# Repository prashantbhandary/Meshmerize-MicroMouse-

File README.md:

# 🤖 Meshmerize MicroMouse Project

> **A comprehensive autonomous line-following and maze-solving robot project featuring multiple hardware iterations, advanced algorithms, and professional PCB designs.**

## 🏆 Competition Achievements

Our MicroMouse has proven its excellence in prestigious robotics competitions:

- 🥇 **1st Place** - Locus, Pulchowk Campus  
- 🥈 **2nd Place** - Delta 5.0, Dharan IOE  
- 🏅 **5th Place** - Techfest, IIT Bombay 2024

<div align="center">

*Certificate of Achievement from IIT Bombay Techfest 2024*

</div>

---

## 📋 Table of Contents

- [🎯 Project Overview](#-project-overview)
- [✨ Key Features](#-key-features)
- [🔧 Hardware Versions](#-hardware-versions)
- [💻 Software Architecture](#-software-architecture)
- [🚀 Getting Started](#-getting-started)
- [📁 Repository Structure](#-repository-structure)
- [🛠️ Installation & Setup](#️-installation--setup)
- [🎮 Usage Instructions](#-usage-instructions)
- [🧠 Algorithms & Control Systems](#-algorithms--control-systems)
- [📷 Project Gallery](#-project-gallery)
- [🤝 Contributing](#-contributing)
- [📄 License](#-license)

---

## 🎯 Project Overview

The **Meshmerize MicroMouse** is an autonomous robot designed to navigate line-following courses and solve complex mazes. This project showcases the evolution of robotics engineering through multiple hardware iterations, from Arduino Nano-based prototypes to advanced ESP32-powered systems.

### What Makes This Project Special?

- **Multiple Hardware Generations**: Evolution from v1.0 to v3.1 with continuous improvements
- **Dual Platform Support**: Both Arduino Nano and ESP32 implementations
- **Professional PCB Design**: Custom-designed circuit boards using KiCad
- **Advanced Algorithms**: LSRB maze-solving with optimized PID control
- **Competition-Tested**: Proven performance in national and international competitions

---

## ✨ Key Features

### 🎯 **Navigation Capabilities**
- **Line Following**: Precise black/white line detection and following
- **Maze Solving**: Autonomous exploration and shortest path execution
- **Multi-Surface Support**: Adaptable to different track conditions

### ⚡ **Performance Optimization**
- **PID Control System**: Smooth and accurate movement control
- **Speed Management**: Adaptive speed control for different track sections
- **Sensor Calibration**: Advanced sensor tuning for reliable detection

### 🔧 **Hardware Excellence**
- **Custom PCB Design**: Professional circuit board layouts
- **Modular Architecture**: Easy maintenance and upgrades
- **Power Management**: Efficient voltage regulation for all components

---

## 🔧 Hardware Versions

<details>
<summary><strong>Arduino Nano Series</strong></summary>

### Version 1.0 - Prototype
- **Microcontroller**: Arduino Nano
- **Motor Driver**: L293D
- **Sensors**: QTR-8A analog sensor array
- **Status**: Initial prototype and testing phase

### Version 2.0 - Enhanced Performance
- **Microcontroller**: Arduino Nano (optimized)
- **Motor Driver**: SparkFun TB6612FNG
- **Sensors**: 8-channel QTR sensor array
- **Improvements**: Better motor control, enhanced PID tuning
- **PCB**: Custom-designed v2.0 PCB

### Version 3.0/3.1 - Professional Grade
- **Microcontroller**: Arduino Nano
- **Features**: Professional PCB design with improved layout
- **Status**: Competition-ready version

</details>

<details>
<summary><strong>ESP32 Series</strong></summary>

### ESP32 Version 1.0
- **Microcontroller**: ESP32 DevKit
- **Development**: PlatformIO-based development
- **Features**: 
  - Wireless capabilities
  - Higher processing power
  - Advanced sensor integration
- **PCB**: Custom ESP32-based PCB design

</details>

---

## 💻 Software Architecture

### Programming Platforms
- **Arduino IDE**: Traditional Arduino Nano development
- **PlatformIO**: Advanced ESP32 development with better library management

### Key Libraries
```cpp
#include <SparkFun_TB6612.h>  // Motor control library
#include <QTRSensors.h>       // Sensor array library
```

### Algorithm Implementation
- **LSRB Algorithm**: Left-Straight-Right-Back priority maze solving
- **PID Control**: Proportional-Integral-Derivative control for smooth movement
- **Path Optimization**: Shortest path calculation and execution

---

## 🚀 Getting Started

### Prerequisites
- Arduino IDE or PlatformIO
- USB cable for programming
- Basic electronics knowledge
- Robotics track or maze for testing

### Quick Setup
1. **Clone the repository**
   ```bash
   git clone https://github.com/prashantbhandary/Meshmerize-MicroMouse-.git
   cd Meshmerize-MicroMouse-
   ```

2. **Choose your platform**
   - For Arduino Nano: Navigate to `ArduinoNano/` folder
   - For ESP32: Navigate to `Esp32/` folder

3. **Select the appropriate version**
   - Pick the version that matches your hardware setup
   - Latest versions recommended for best performance

---

## 📁 Repository Structure

```
📦 Meshmerize-MicroMouse-
├── 🔧 ArduinoNano/
│   ├── 🧪 arduno_nano_v1_TestingCode/
│   │   ├── arduino_sensor_test2.0/
│   │   ├── black_line_maze_2.0/
│   │   ├── motor-testing/
│   │   └── night_nano/
│   ├── 📋 micro_mouse_v1-files/
│   │   ├── codes/ (Line follower, maze solving, testing)
│   │   └── design/ (3D models, PCB files)
│   ├── 🚀 micro_mouse_v2-files/
│   │   ├── BlackLineMazeFinal_v2-Code/
│   │   ├── LineFollowerPid_v2-Code/
│   │   ├── WhiteLineMazeFinal_v2-Code/
│   │   └── micro_mouse_v2-pcb/
│   └── 🏆 micro_mouse_v3_files/
│       ├── micro_mouse_prashant/
│       ├── micro_mouse_v3.0-PCB/
│       └── micro_mouse_v3.1-PCB/
├── 📡 Esp32/
│   ├── LineFolloweEsp32_v1_code/
│   ├── micromouseEsp32_v1_PCB/
│   └── testing_esp32_v1_code/
├── 📸 IMG/
│   ├── Competition videos and images
│   └── Robot demonstration media
└── 📖 README.md
```

---

## 🛠️ Installation & Setup

### For Arduino Nano Versions

1. **Install Required Libraries**
   ```
   - SparkFun TB6612 Motor Driver Library
   - QTRSensors Library
   ```

2. **Hardware Setup**
   - Connect QTR sensors to analog pins A0-A7
   - Wire motor drivers according to pin definitions
   - Connect control switches and LED indicators

3. **Upload Code**
   - Open the desired version in Arduino IDE
   - Select Arduino Nano board
   - Upload the code

### For ESP32 Version

1. **PlatformIO Setup**
   ```bash
   cd Esp32/LineFolloweEsp32_v1_code/Micromouse/
   pio run --target upload
   ```

2. **Hardware Configuration**
   - Follow ESP32 pin definitions in the code
   - Ensure proper power supply (3.3V/5V compatibility)

---

## 🎮 Usage Instructions

### Initial Setup
1. **Calibration Phase**
   - Press switch 1 to start sensor calibration
   - Move the robot over the line during calibration
   - LED indicator confirms successful calibration

2. **Mode Selection**
   - **Switch 2**: Left-hand rule (LHS) priority
   - **Switch 3**: Right-hand rule (RHS) priority

3. **Start Operation**
   - Press switch 1 again to begin line following/maze solving
   - Robot will autonomously navigate the course

### Operating Modes

#### Line Following Mode
- Robot follows black line on white surface (or vice versa)
- PID control ensures smooth tracking
- Adaptive speed control for optimal performance

#### Maze Solving Mode
- **Exploration Phase**: Robot maps the entire maze
- **Optimization Phase**: Calculates shortest path
- **Execution Phase**: Runs the optimized route

---

## 🧠 Algorithms & Control Systems

### LSRB Algorithm (Left-Straight-Right-Back)
```cpp
// Priority decision making
if (left_path_available) {
    turn_left();
} else if (straight_path_available) {
    move_forward();
} else if (right_path_available) {
    turn_right();
} else {
    turn_back(); // Dead end
}
```

### PID Control System
```cpp
// PID calculation for smooth movement
error = sensor_position - desired_position;
derivative = error - lastError;
correction = (kp * error) + (kd * derivative);
motor_speed_adjustment = base_speed ± correction;
```

### Key Parameters
- **Base Speed**: 130-255 (adjustable per version)
- **Kp (Proportional)**: 0.05-0.151 (tuned per hardware)
- **Kd (Derivative)**: 0.1-0.8 (optimized for stability)

---

## 📷 Project Gallery

<div align="center">

### 🤖 Robot Images
 | 
:---: | :---:
*Side Profile* | *Front View*

*Competition Ready Configuration*

### 🎥 Demo Videos
▶️ **[Watch MicroMouse in Action](./IMG/iit_bombay.mp4)**  
*Live demonstration from IIT Bombay competition*

▶️ **[Advanced Maze Solving Demo](./IMG/469240304_8275277389243894_8094127931744390612_n.mp4)**  
*Complex maze navigation showcase*

</div>

---

## 🤝 Contributing

We welcome contributions to improve the MicroMouse project! Here's how you can help:

### Ways to Contribute
- 🐛 **Bug Reports**: Found an issue? Let us know!
- 💡 **Feature Requests**: Suggest new capabilities
- 🔧 **Code Improvements**: Optimize algorithms or add new features
- 📚 **Documentation**: Help improve guides and tutorials
- 🔬 **Testing**: Try different hardware configurations

### Development Setup
1. Fork the repository
2. Create a feature branch (`git checkout -b feature/AmazingFeature`)
3. Make your changes
4. Test thoroughly with hardware
5. Commit your changes (`git commit -m 'Add AmazingFeature'`)
6. Push to the branch (`git push origin feature/AmazingFeature`)
7. Open a Pull Request

---

## 📞 Contact & Support

- **Project Maintainer**: Prashant Bhandary
- **GitHub**: [@prashantbhandary](https://github.com/prashantbhandary)
- **Repository**: [Meshmerize-MicroMouse-](https://github.com/prashantbhandary/Meshmerize-MicroMouse-)
- **Portfolio Website**: 🌐 [bhandari-prashant.com.np](https://bhandari-prashant.com.np)

### Getting Help
- 📋 **Issues**: Use GitHub Issues for bug reports
- 💬 **Discussions**: Join repository discussions for general questions
- 📖 **Wiki**: Check the wiki for detailed guides (coming soon)

---

## 📄 License

This project is licensed under the MIT License - see the [LICENSE](LICENSE) file for details.

### What this means:
- ✅ Use in personal and commercial projects
- ✅ Modify and distribute freely
- ✅ Include in other projects
- 📋 Attribution required

---

<div align="center">

### 🌟 Star this project if you found it helpful!

**Made with ❤️ by the Robotics Team, WRC**

*"Engineering the future, one algorithm at a time."*

</div>
  
### Achievements:
1. Winner at **Locus 2025**, Pulchowk IOE.
2. 1st Runner-up at **Delta 5.0 ERC**, Dharan IOE.
3. Top 5 finish at **Techfest, IIT Bombay 2024** amidst tough competition.

This project was a huge learning experience, teaching us valuable lessons in algorithm optimization, hardware design, and problem-solving.

## Special Thanks:

- **Teammates and Mentors**: Aabiskar Regmi, Sanjog Sapkota, Siddartha Gupta

Can’t wait to tackle even bigger challenges next! 🚀

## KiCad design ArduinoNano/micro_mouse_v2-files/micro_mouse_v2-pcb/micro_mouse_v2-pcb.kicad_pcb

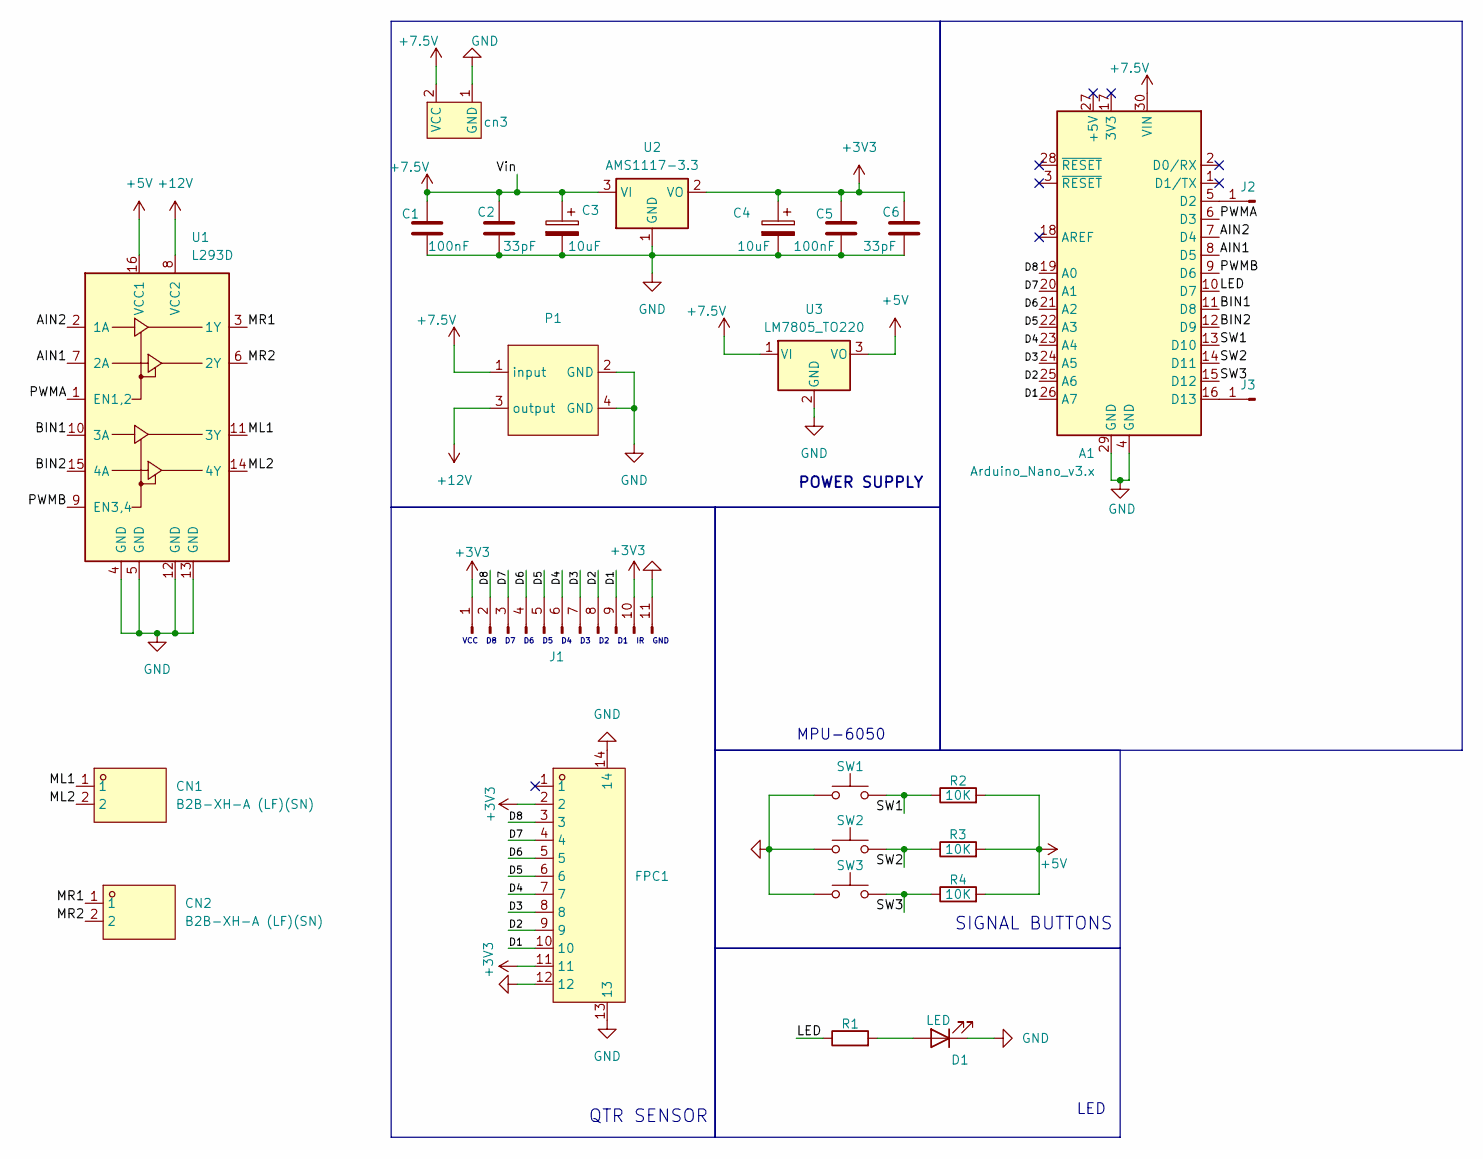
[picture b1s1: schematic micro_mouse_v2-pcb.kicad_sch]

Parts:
A1: Arduino_Nano_v3.x; Arduino_Nano
C1, C5: 100nF; C_0805_2012Metric; lcsc C100072
C2, C6: 33pF; C_0805_2012Metric; lcsc C100072
C3, C4: 10uF; C_0805_2012Metric; lcsc C119052
CN1, CN2: B2B-XH-A (LF)(SN); CONN-TH_B2B-XH-A-LF-SN; LCSC Part C158012
D1: LED; LED0603-RD
FPC1: FPC-05F-12PH20; FPC-SMD_12P-P0.50_FPC-05F-12PH20; LCSC Part C2856799
J1: Conn_01x11_Pin; PinHeader_1x11_P2.54mm_Vertical
J2, J3: Conn_01x01_Pin; PinHeader_1x01_P2.54mm_Vertical
P1: buck_boost converter
R1: R; R_0603_1608Metric
R2, R3, R4: 10K; R_0603_1608Metric
SW1, SW2, SW3: SW_Push; SW-SMD_L6.0-W3.3-LS8.0
U1: L293D; DIP-16_W7.62mm
U2: AMS1117-3.3; SOT-223-3_TabPin2
U3: LM7805_TO220; TO-220-3_Vertical
cn3: PinSocket_1x02_P2.54mm_Vertical

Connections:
+3V3: C4.1, C5.1, C6.1, FPC1.2, FPC1.11, J1.1, J1.10, U2.2 (VO)
+5V: R2.2, R3.2, R4.2, U1.16 (VCC1), U3.3 (VO)
+7.5V: A1.30 (VIN), C1.1, C2.1, C3.1, P1.1 (input), U2.3 (VI), U3.1 (VI), cn3.2 (VCC)
+12V: P1.3 (output), U1.8 (VCC2)
/AIN1: A1.8 (D5), U1.7 (2A)
/AIN2: A1.7 (D4), U1.2 (1A)
/BIN1: A1.11 (D8), U1.10 (3A)
/BIN2: A1.12 (D9), U1.15 (4A)
/D1: A1.26 (A7), FPC1.10, J1.9
/D2: A1.25 (A6), FPC1.9, J1.8
/D3: A1.24 (A5), FPC1.8, J1.7
/D4: A1.23 (A4), FPC1.7, J1.6
/D5: A1.22 (A3), FPC1.6, J1.5
/D6: A1.21 (A2), FPC1.5, J1.4
/D7: A1.20 (A1), FPC1.4, J1.3
/D8: A1.19 (A0), FPC1.3, J1.2
/LED: A1.10 (D7), R1.1
/ML1: CN1.1, U1.11 (3Y)
/ML2: CN1.2, U1.14 (4Y)
/MR1: CN2.1, U1.3 (1Y)
/MR2: CN2.2, U1.6 (2Y)
/PWMA: A1.6 (D3), U1.1 (EN1,2)
/PWMB: A1.9 (D6), U1.9 (EN3,4)
/SW1: A1.13 (D10), R2.1, SW1.2
/SW2: A1.14 (D11), R3.1, SW2.2
/SW3: A1.15 (D12), R4.1, SW3.2
GND: A1.4 (GND), A1.29 (GND), C1.2, C2.2, C3.2, C4.2, C5.2, C6.2, D1.1 (K), FPC1.12, FPC1.13, FPC1.14, J1.11, P1.2 (GND), P1.4 (GND), SW1.1, SW2.1, SW3.1, U1.4 (GND), U1.5 (GND), U1.12 (GND), U1.13 (GND), U2.1 (GND), U3.2 (GND), cn3.1 (GND)
unnamed: A1.5 (D2), J2.1
unnamed: A1.16 (D13), J3.1
unnamed: D1.2 (A), R1.2

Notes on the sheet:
QTR SENSOR
LED
SIGNAL BUTTONS
POWER SUPPLY
VCC D8 D7 D6 D5 D4 D3 D2 D1 IR GND
MPU-6050

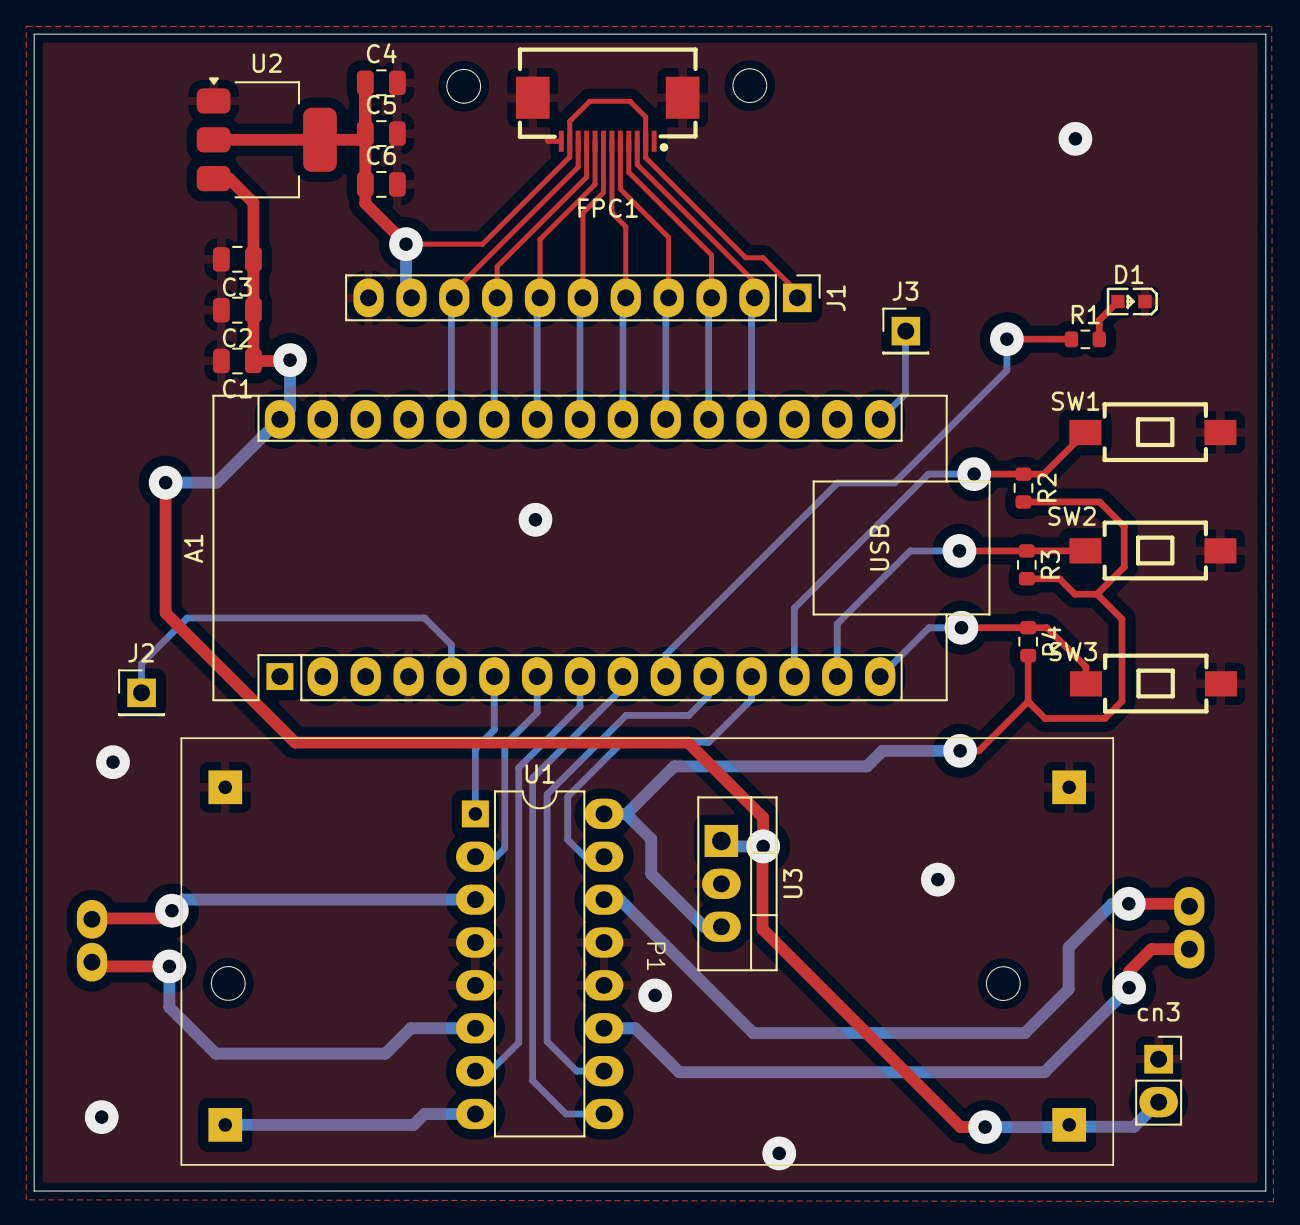
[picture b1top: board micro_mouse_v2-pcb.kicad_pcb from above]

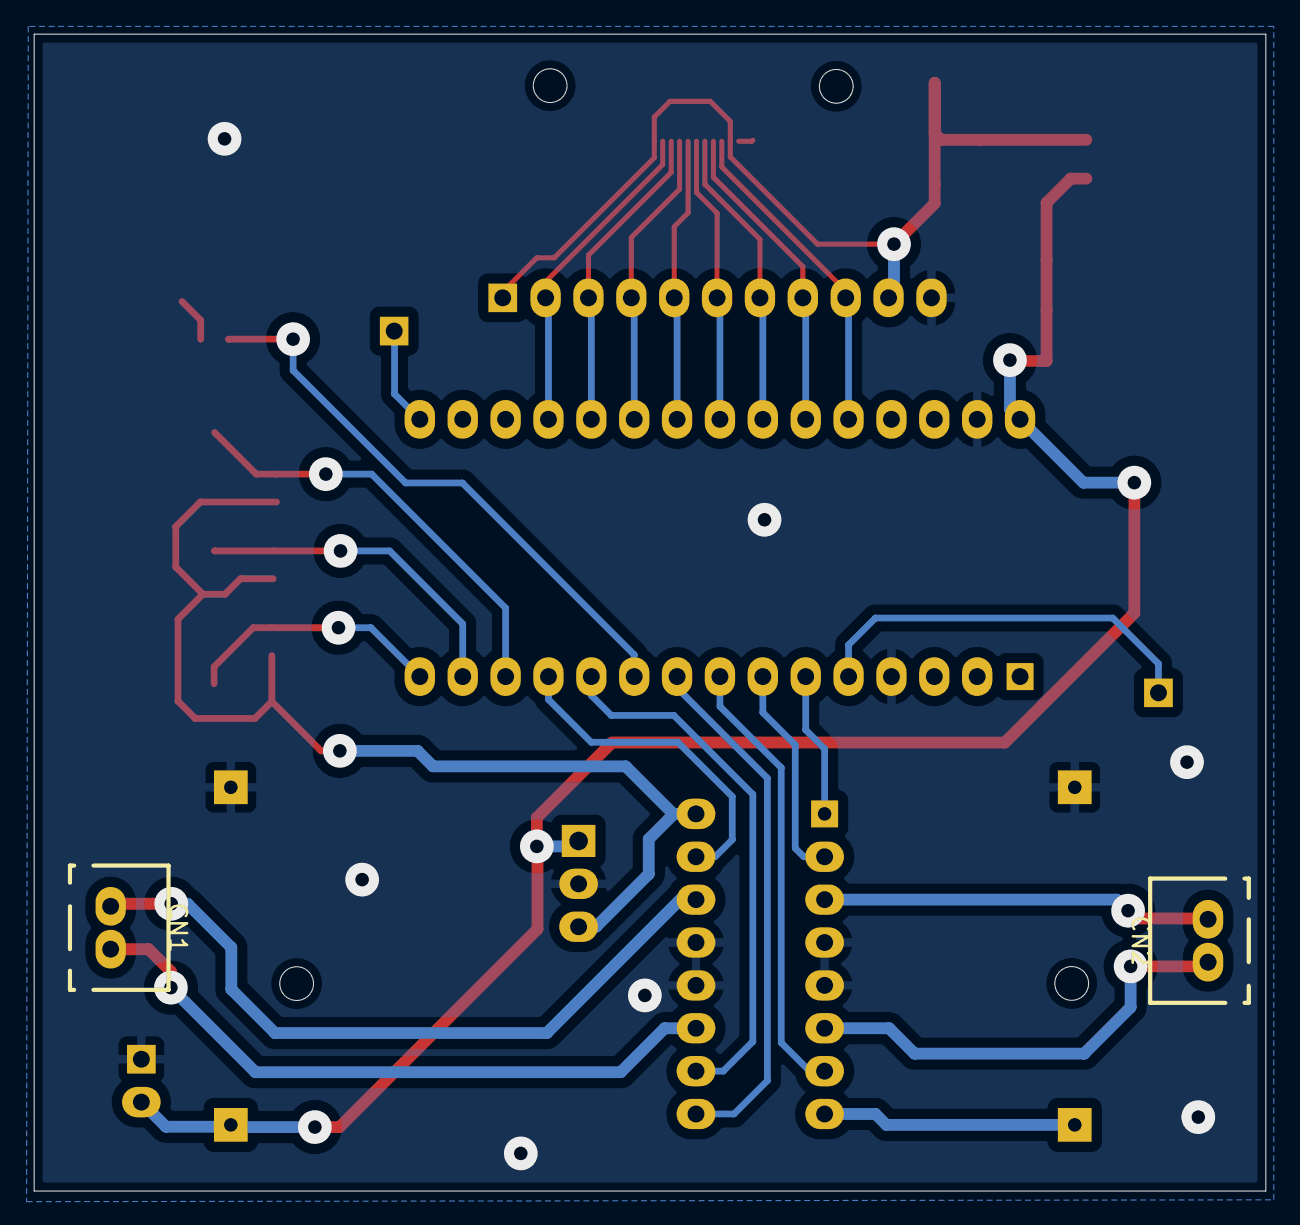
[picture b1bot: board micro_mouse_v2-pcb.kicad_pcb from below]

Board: 2 copper layers, 73.0 x 68.5 mm, 26 parts (2 on the bottom side), 30 nets.

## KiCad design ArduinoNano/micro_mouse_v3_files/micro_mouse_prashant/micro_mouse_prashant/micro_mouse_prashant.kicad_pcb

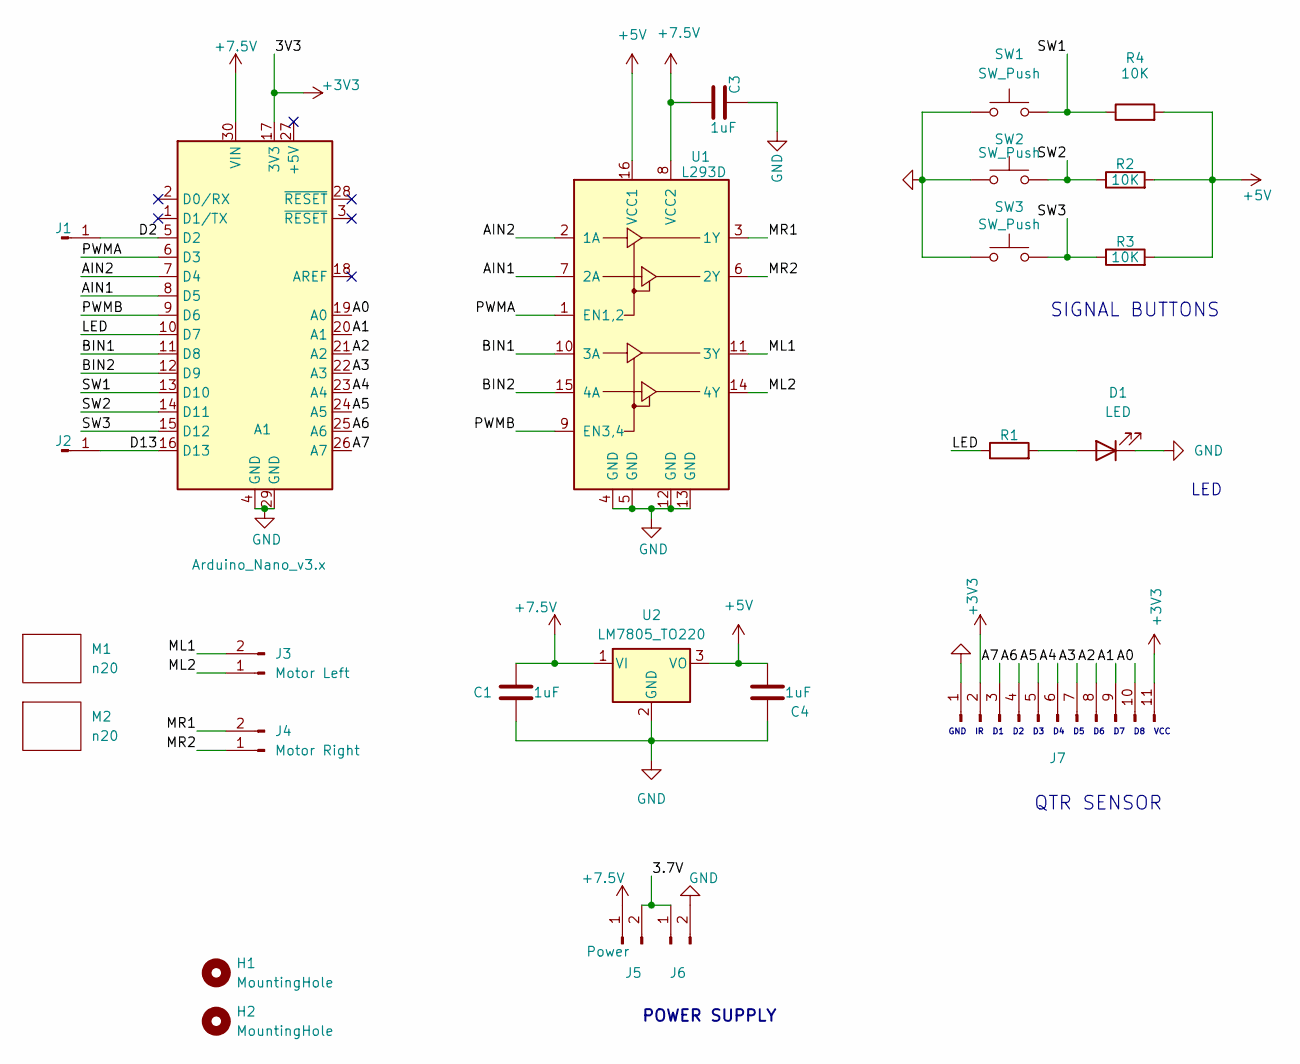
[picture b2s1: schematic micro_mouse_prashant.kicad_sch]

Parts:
A1: Arduino_Nano_v3.x; Arduino_Nano
C1: 1uF; C_Radial_D6.3mm_H7.0mm_P2.50mm; lcsc C100072
C3, C4: 1uF; C_Radial_D6.3mm_H11.0mm_P2.50mm; lcsc C100072
D1: LED; LED_D4.0mm
H1, H2: MountingHole; MountingHole_2.5mm
J1, J2: Conn_01x01_Pin; PinHeader_1x01_P2.54mm_Vertical
J3: Motor Left; PinHeader_1x02_P2.54mm_Vertical
J4: Motor Right; PinHeader_1x02_P2.54mm_Vertical
J5, J6: Power; PinHeader_1x02_P2.54mm_Vertical
J7: Conn_01x11_Pin; PinHeader_1x11_P2.54mm_Vertical
M1, M2: n20; N20 Gear Motor
R1: R; R_Axial_DIN0207_L6.3mm_D2.5mm_P7.62mm_Horizontal
R2, R3, R4: 10K; R_Axial_DIN0207_L6.3mm_D2.5mm_P7.62mm_Horizontal
SW1, SW2, SW3: SW_Push; SW_PUSH_6mm
U1: L293D; DIP-16_W7.62mm
U2: LM7805_TO220; TO-220-3_Vertical

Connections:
+3V3: A1.17 (3V3), J7.2, J7.11
+5V: C4.1, R2.2, R3.2, R4.2, U1.16 (VCC1), U2.3 (VO)
+7.5V: A1.30 (VIN), C1.1, C3.2, J5.1, U1.8 (VCC2), U2.1 (VI)
/3.7V: J5.2, J6.1
/A0: A1.19 (A0), J7.10
/A1: A1.20 (A1), J7.9
/A2: A1.21 (A2), J7.8
/A3: A1.22 (A3), J7.7
/A4: A1.23 (A4), J7.6
/A5: A1.24 (A5), J7.5
/A6: A1.25 (A6), J7.4
/A7: A1.26 (A7), J7.3
/AIN1: A1.8 (D5), U1.7 (2A)
/AIN2: A1.7 (D4), U1.2 (1A)
/BIN1: A1.11 (D8), U1.10 (3A)
/BIN2: A1.12 (D9), U1.15 (4A)
/D2: A1.5 (D2), J1.1
/D13: A1.16 (D13), J2.1
/LED: A1.10 (D7), R1.1
/ML1: J3.2, U1.11 (3Y)
/ML2: J3.1, U1.14 (4Y)
/MR1: J4.2, U1.3 (1Y); also elsewhere on the board
/MR2: J4.1, U1.6 (2Y); also elsewhere on the board
/PWMA: A1.6 (D3), U1.1 (EN1,2)
/PWMB: A1.9 (D6), U1.9 (EN3,4)
/SW1: A1.13 (D10), R4.1, SW1.2
/SW2: A1.14 (D11), R2.1, SW2.2
/SW3: A1.15 (D12), R3.1, SW3.2
GND: A1.4 (GND), A1.29 (GND), C1.2, C3.1, C4.2, D1.1 (K), J6.2, J7.1, SW1.1, SW2.1, SW3.1, U1.4 (GND), U1.5 (GND), U1.12 (GND), U1.13 (GND), U2.2 (GND)
unnamed: D1.2 (A), R1.2

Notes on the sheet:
LED
SIGNAL BUTTONS
QTR SENSOR
POWER SUPPLY
GND IR D1 D2 D3 D4 D5 D6 D7 D8 VCC

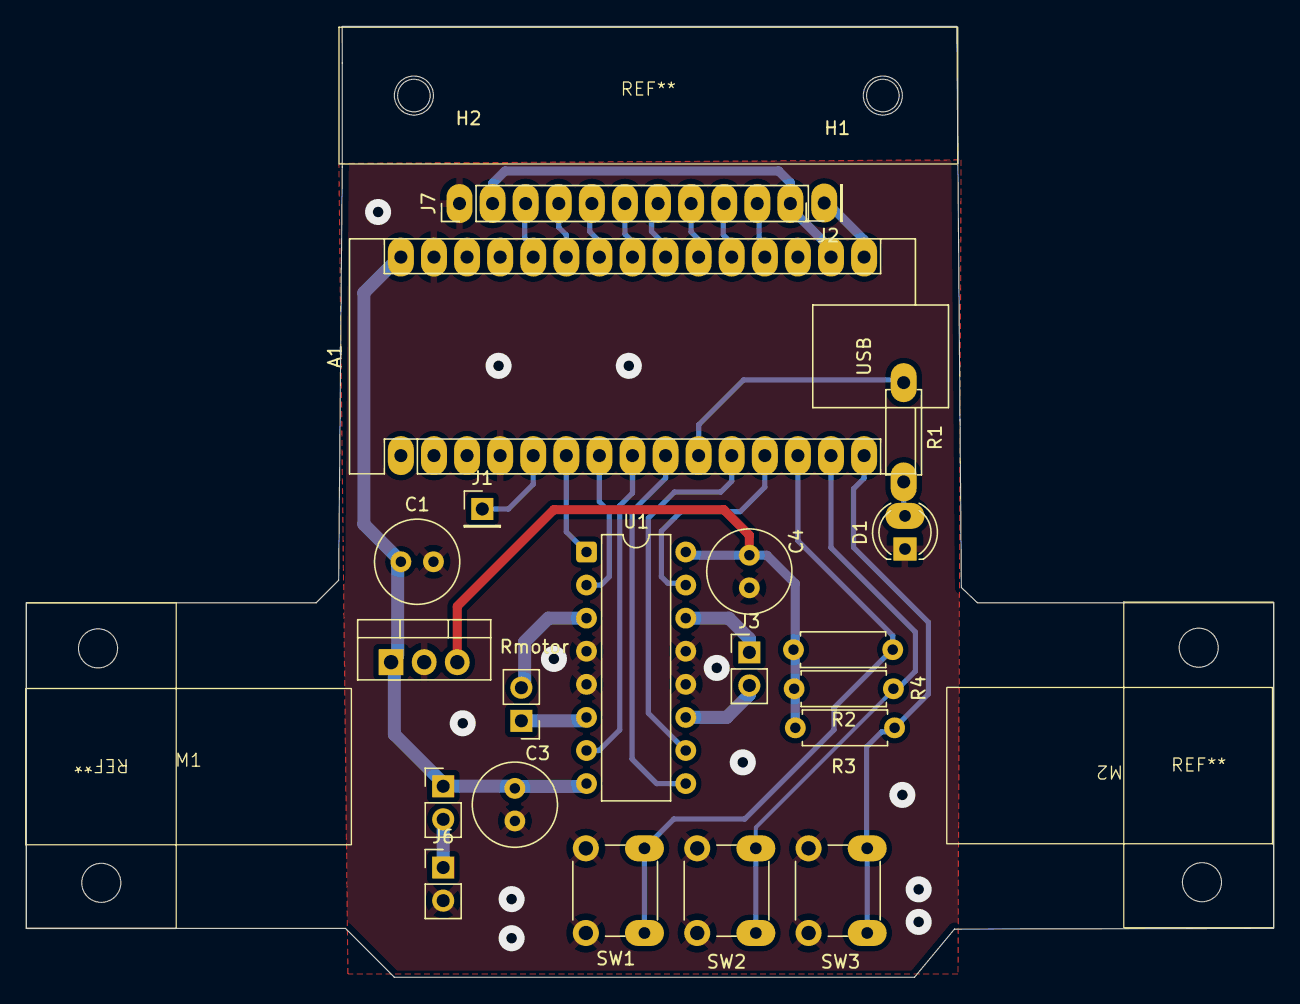
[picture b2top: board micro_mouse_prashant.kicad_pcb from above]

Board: 2 copper layers, 95.8 x 73.0 mm, 25 parts (0 on the bottom side), 30 nets.

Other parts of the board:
Rmotor: Motor Right; PinHeader_1x02_P2.54mm_Vertical

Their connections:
/MR1: Rmotor.2; also elsewhere on the board
/MR2: Rmotor.1; also elsewhere on the board

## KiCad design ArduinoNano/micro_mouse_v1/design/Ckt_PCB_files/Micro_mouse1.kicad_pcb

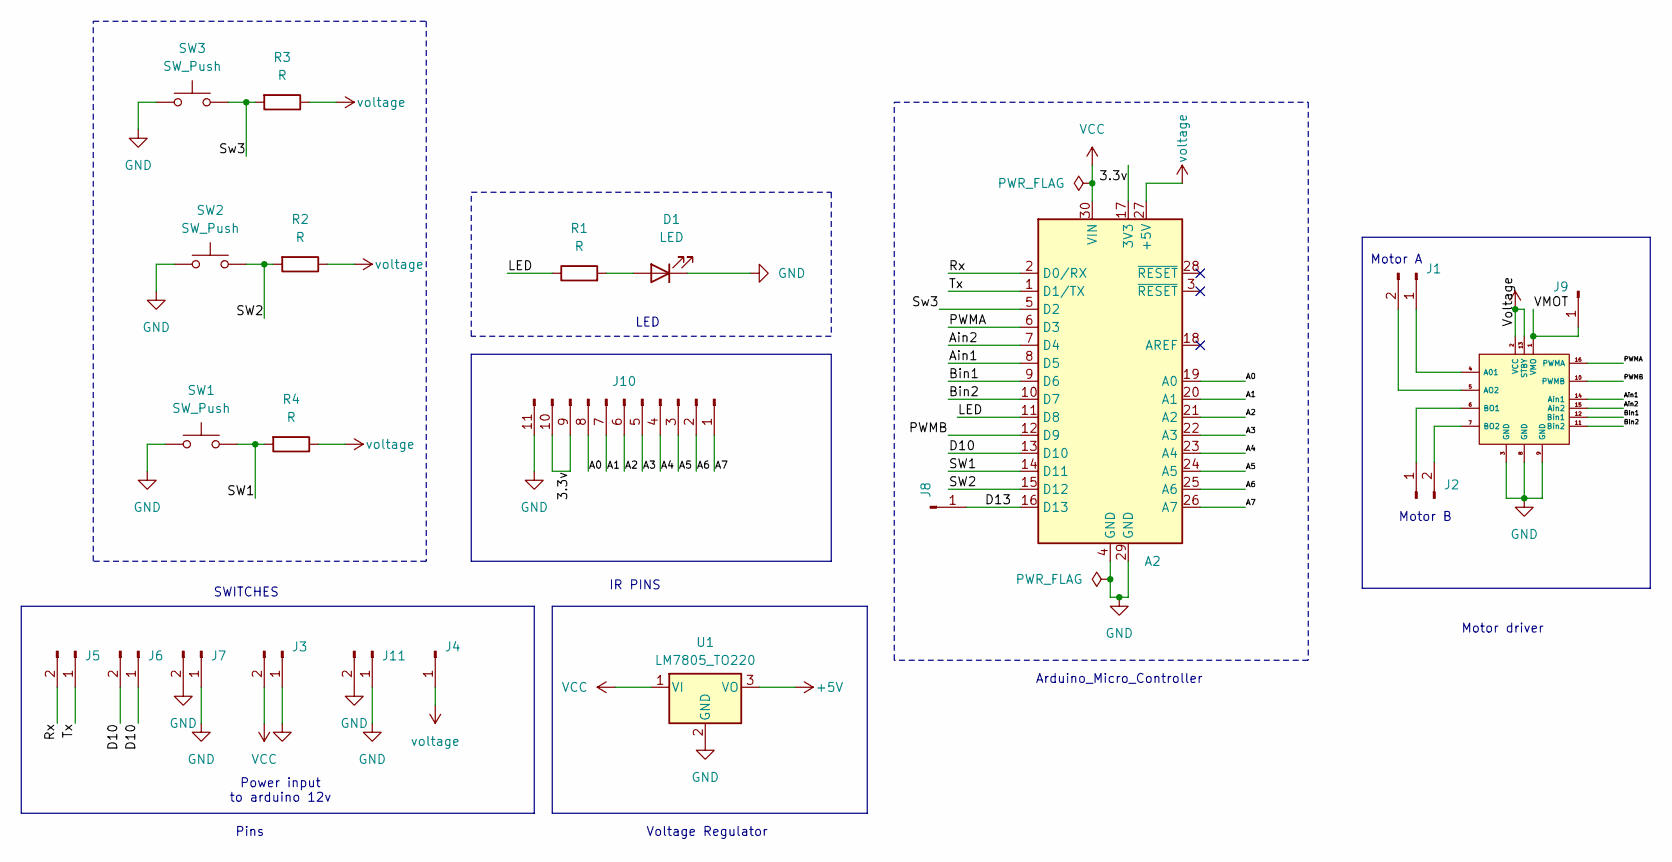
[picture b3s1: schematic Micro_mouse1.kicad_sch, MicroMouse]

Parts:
A2: Arduino_Nano_v3.x; Arduino_Nano
D1: LED; LED_D1.8mm_W1.8mm_H2.4mm_Horizontal_O1.27mm_Z1.6mm
J1, J2, J3, J5, J6, J7, J11: Conn_01x02_Pin; PinSocket_1x02_P2.54mm_Vertical
J4, J8, J9: Conn_01x01_Pin; PinSocket_1x01_P2.54mm_Vertical
J10: Conn_01x11_Pin; PinSocket_1x11_P2.54mm_Vertical
MD1: tbfng motor driver
R1, R2, R3, R4: R; R_Axial_DIN0204_L3.6mm_D1.6mm_P5.08mm_Horizontal
SW1, SW2, SW3: SW_Push; SW_PUSH_6mm
U1: LM7805_TO220; TO-220-3_Vertical

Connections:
+5V: MD1.2 (VCC), MD1.13 (STBY), U1.3 (VO)
/3.3v: A2.17 (3V3), J10.9, J10.10
/A0: A2.19 (A0), J10.8
/A1: A2.20 (A1), J10.7
/A2: A2.21 (A2), J10.6
/A3: A2.22 (A3), J10.5
/A4: A2.23 (A4), J10.4
/A5: A2.24 (A5), J10.3
/A6: A2.25 (A6), J10.2
/A7: A2.26 (A7), J10.1
/Ain1: A2.8 (D5), MD1.14 (Ain1)
/Ain2: A2.7 (D4), MD1.15 (Ain2)
/Bin1: A2.9 (D6), MD1.12 (Bin1)
/Bin2: A2.10 (D7), MD1.11 (Bin2)
/D10: A2.13 (D10), J6.1, J6.2
/D13: A2.16 (D13), J8.1
/LED: A2.11 (D8), R1.1
/PWMA: A2.6 (D3), MD1.16 (PWMA)
/PWMB: A2.12 (D9), MD1.10 (PWMB)
/Rx: A2.2 (D0/RX), J5.2
/SW1: A2.14 (D11), R4.2, SW1.2
/SW2: A2.15 (D12), R2.2, SW2.2
/Sw3: A2.5 (D2), R3.2, SW3.2
/Tx: A2.1 (D1/TX), J5.1
/VMOT: J9.1, MD1.1 (VMO)
GND: A2.4 (GND), A2.29 (GND), D1.1 (K), J3.1, J7.1, J7.2, J10.11, J11.1, J11.2, MD1.3 (GND), MD1.8 (GND), MD1.9 (GND), SW1.1, SW2.1, SW3.1, U1.2 (GND)
unnamed: D1.2 (A), R1.2
unnamed: J1.1, MD1.4 (A01)
unnamed: J1.2, MD1.5 (AO2)
unnamed: J2.1, MD1.6 (BO1)
unnamed: J2.2, MD1.7 (BO2)
VCC: A2.30 (VIN), J3.2, U1.1 (VI)
voltage: A2.27 (+5V), J4.1, R2.1, R3.1, R4.1

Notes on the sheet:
Motor A
Arduino_Micro_Controller
Motor driver
Voltage Regulator
Power input to arduino 12v
SWITCHES
Pins
LED
Motor B
IR PINS

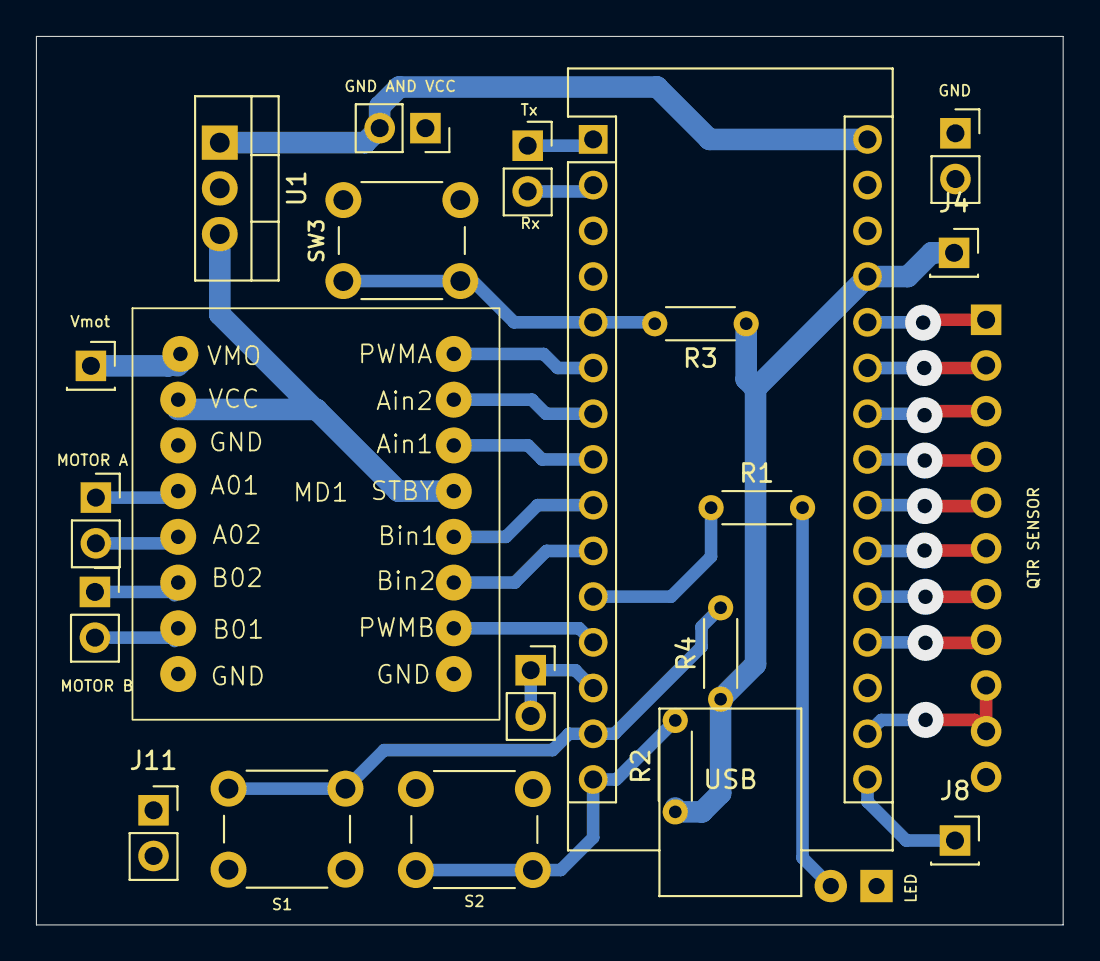
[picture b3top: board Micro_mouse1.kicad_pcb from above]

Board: 2 copper layers, 57.0 x 49.4 mm, 22 parts (1 on the bottom side), 33 nets.

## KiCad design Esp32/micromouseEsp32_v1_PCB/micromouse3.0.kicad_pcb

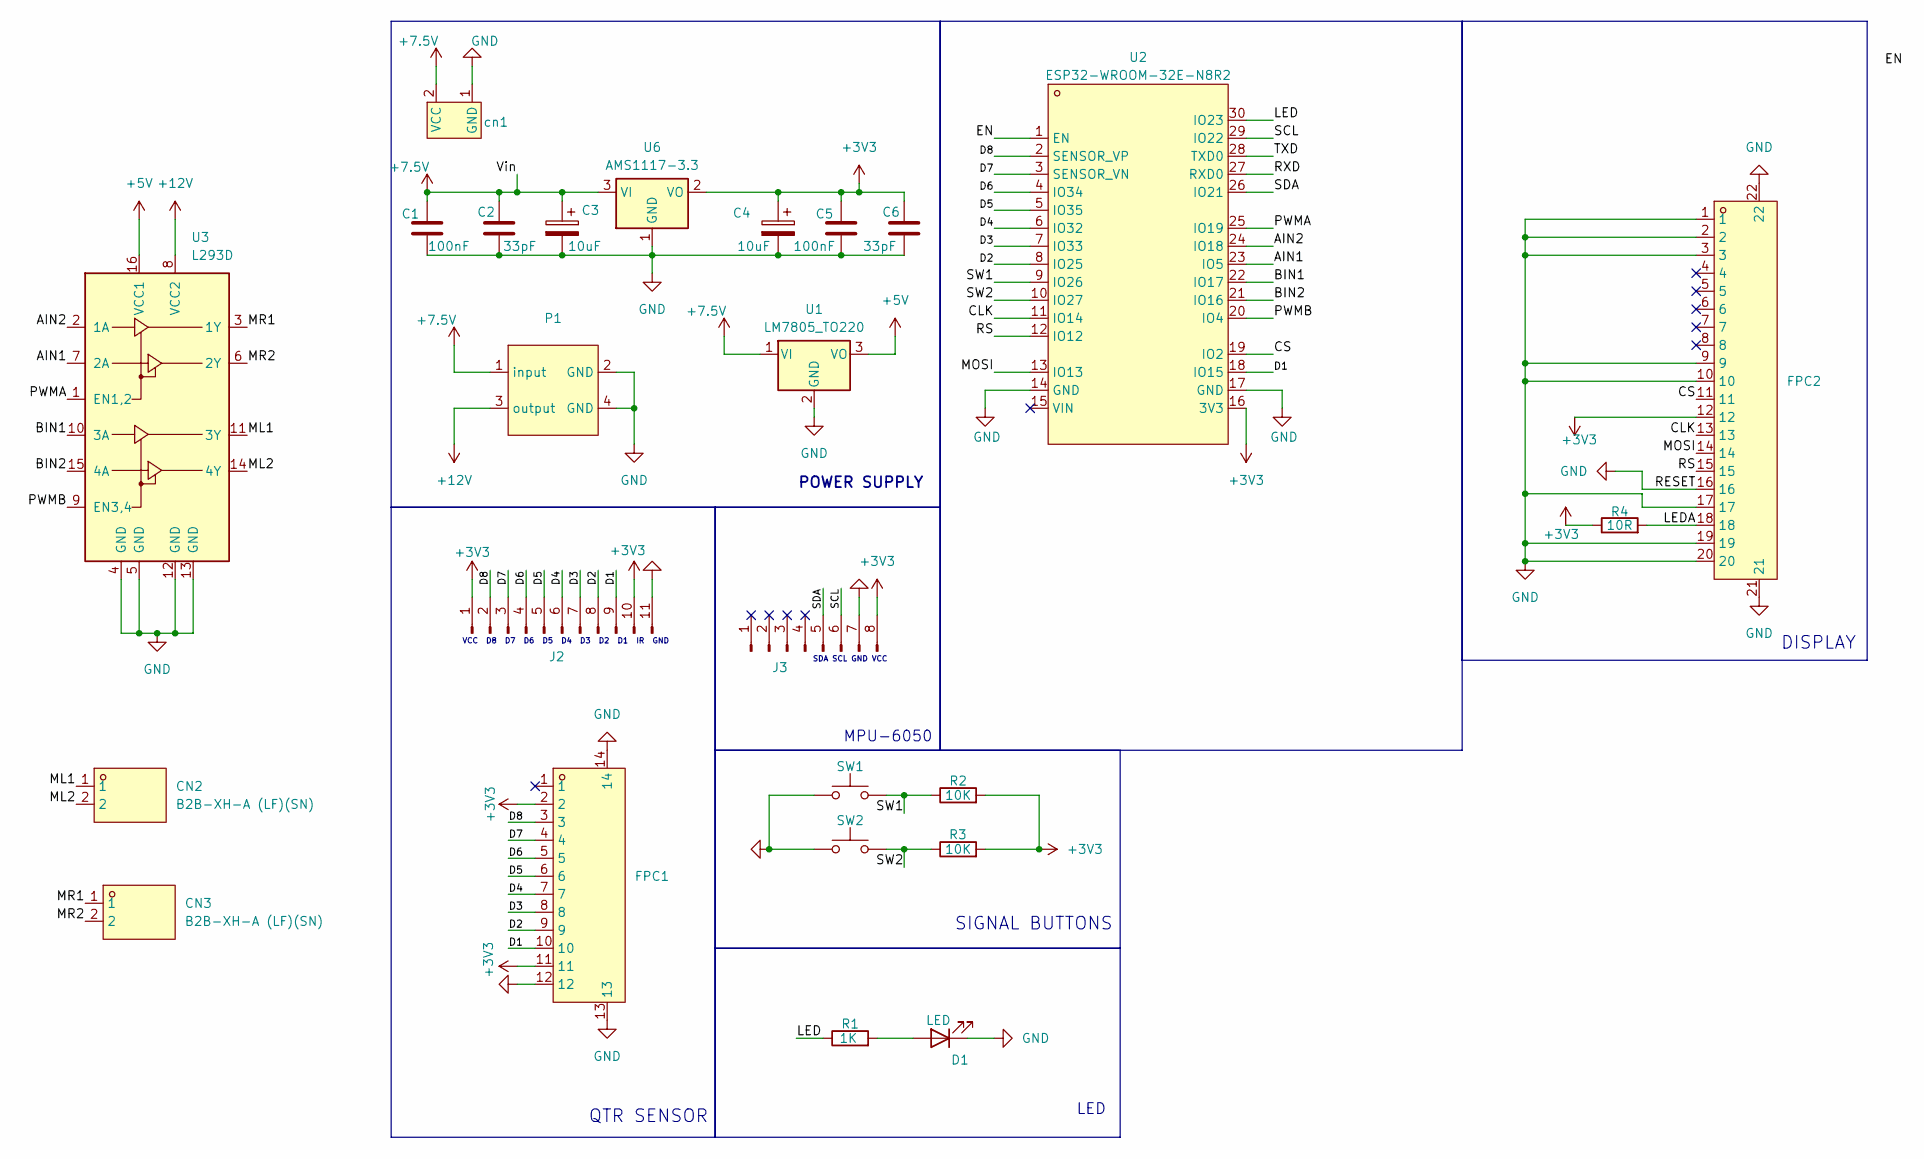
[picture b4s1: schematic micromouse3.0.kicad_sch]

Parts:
C1, C5: 100nF; C_0805_2012Metric; lcsc C100072
C2, C6: 33pF; C_0805_2012Metric; lcsc C100072
C3, C4: 10uF; C_0805_2012Metric; lcsc C119052
CN2, CN3: B2B-XH-A (LF)(SN); CONN-TH_B2B-XH-A-LF-SN; LCSC Part C158012
D1: LED; LED0603-RD
FPC1: FPC-05F-12PH20; FPC-SMD_12P-P0.50_FPC-05F-12PH20; LCSC Part C2856799
FPC2: FPC-05F-20PH20; FPC-SMD_20P-P0.50_XUNPU_FPC-05F-20PH20; LCSC Part C2856803
J2: Conn_01x11_Pin; PinHeader_1x11_P2.54mm_Vertical
J3: Conn_01x08_Pin; PinHeader_1x08_P2.54mm_Vertical
P1: buck_boost converter
R1: 1K; R_0603_1608Metric
R2, R3: 10K; R_0603_1608Metric
R4: 10R; R_0603_1608Metric
SW1, SW2: SW_Push; SW-SMD_L6.0-W3.3-LS8.0
U1: LM7805_TO220; TO-220-3_Vertical
U2: ESP32-WROOM-32E-N8R2; esp32 dev board; LCSC Part C5361945
U3: L293D; DIP-16_W7.62mm
U6: AMS1117-3.3; SOT-223-3_TabPin2
cn1: PinSocket_1x02_P2.54mm_Vertical

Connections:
+3V3: C4.1, C5.1, C6.1, FPC1.2, FPC1.11, FPC2.12, J2.1, J2.10, J3.8, R2.2, R3.2, R4.1, U2.16 (3V3), U6.2 (VO)
+5V: U1.3 (VO), U3.16 (VCC1)
+7.5V: C1.1, C2.1, C3.1, P1.1 (input), U1.1 (VI), U6.3 (VI), cn1.2 (VCC)
+12V: P1.3 (output), U3.8 (VCC2)
/AIN1: U2.23 (IO5), U3.7 (2A)
/AIN2: U2.24 (IO18), U3.2 (1A)
/BIN1: U2.22 (IO17), U3.10 (3A)
/BIN2: U2.21 (IO16), U3.15 (4A)
/CLK: FPC2.13, U2.11 (IO14)
/CS: FPC2.11, U2.19 (IO2)
/D1: FPC1.10, J2.9, U2.18 (IO15)
/D2: FPC1.9, J2.8, U2.8 (IO25)
/D3: FPC1.8, J2.7, U2.7 (IO33)
/D4: FPC1.7, J2.6, U2.6 (IO32)
/D5: FPC1.6, J2.5, U2.5 (IO35)
/D6: FPC1.5, J2.4, U2.4 (IO34)
/D7: FPC1.4, J2.3, U2.3 (SENSOR_VN)
/D8: FPC1.3, J2.2, U2.2 (SENSOR_VP)
/EN: U2.1 (EN)
/LED: R1.1, U2.30 (IO23)
/LEDA: FPC2.18, R4.2
/ML1: CN2.1, U3.11 (3Y)
/ML2: CN2.2, U3.14 (4Y)
/MOSI: FPC2.14, U2.13 (IO13)
/MR1: CN3.1, U3.3 (1Y)
/MR2: CN3.2, U3.6 (2Y)
/PWMA: U2.25 (IO19), U3.1 (EN1,2)
/PWMB: U2.20 (IO4), U3.9 (EN3,4)
/RS: FPC2.15, U2.12 (IO12)
/RXD: U2.27 (RXD0)
/SCL: J3.6, U2.29 (IO22)
/SDA: J3.5, U2.26 (IO21)
/SW1: R2.1, SW1.2, U2.9 (IO26)
/SW2: R3.1, SW2.2, U2.10 (IO27)
/TXD: U2.28 (TXD0)
GND: C1.2, C2.2, C3.2, C4.2, C5.2, C6.2, D1.1 (K), FPC1.12, FPC1.13, FPC1.14, FPC2.1, FPC2.2, FPC2.3, FPC2.9, FPC2.10, FPC2.16, FPC2.17, FPC2.19, FPC2.20, FPC2.21, FPC2.22, J2.11, J3.7, P1.2 (GND), P1.4 (GND), SW1.1, SW2.1, U1.2 (GND), U2.14 (GND), U2.17 (GND), U3.4 (GND), U3.5 (GND), U3.12 (GND), U3.13 (GND), U6.1 (GND), cn1.1 (GND)
unnamed: D1.2 (A), R1.2

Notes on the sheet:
SDA SCL GND VCC
SIGNAL BUTTONS
MPU-6050
DISPLAY
POWER SUPPLY
QTR SENSOR
LED
VCC D8 D7 D6 D5 D4 D3 D2 D1 IR GND

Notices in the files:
README.md:
License: MIT
